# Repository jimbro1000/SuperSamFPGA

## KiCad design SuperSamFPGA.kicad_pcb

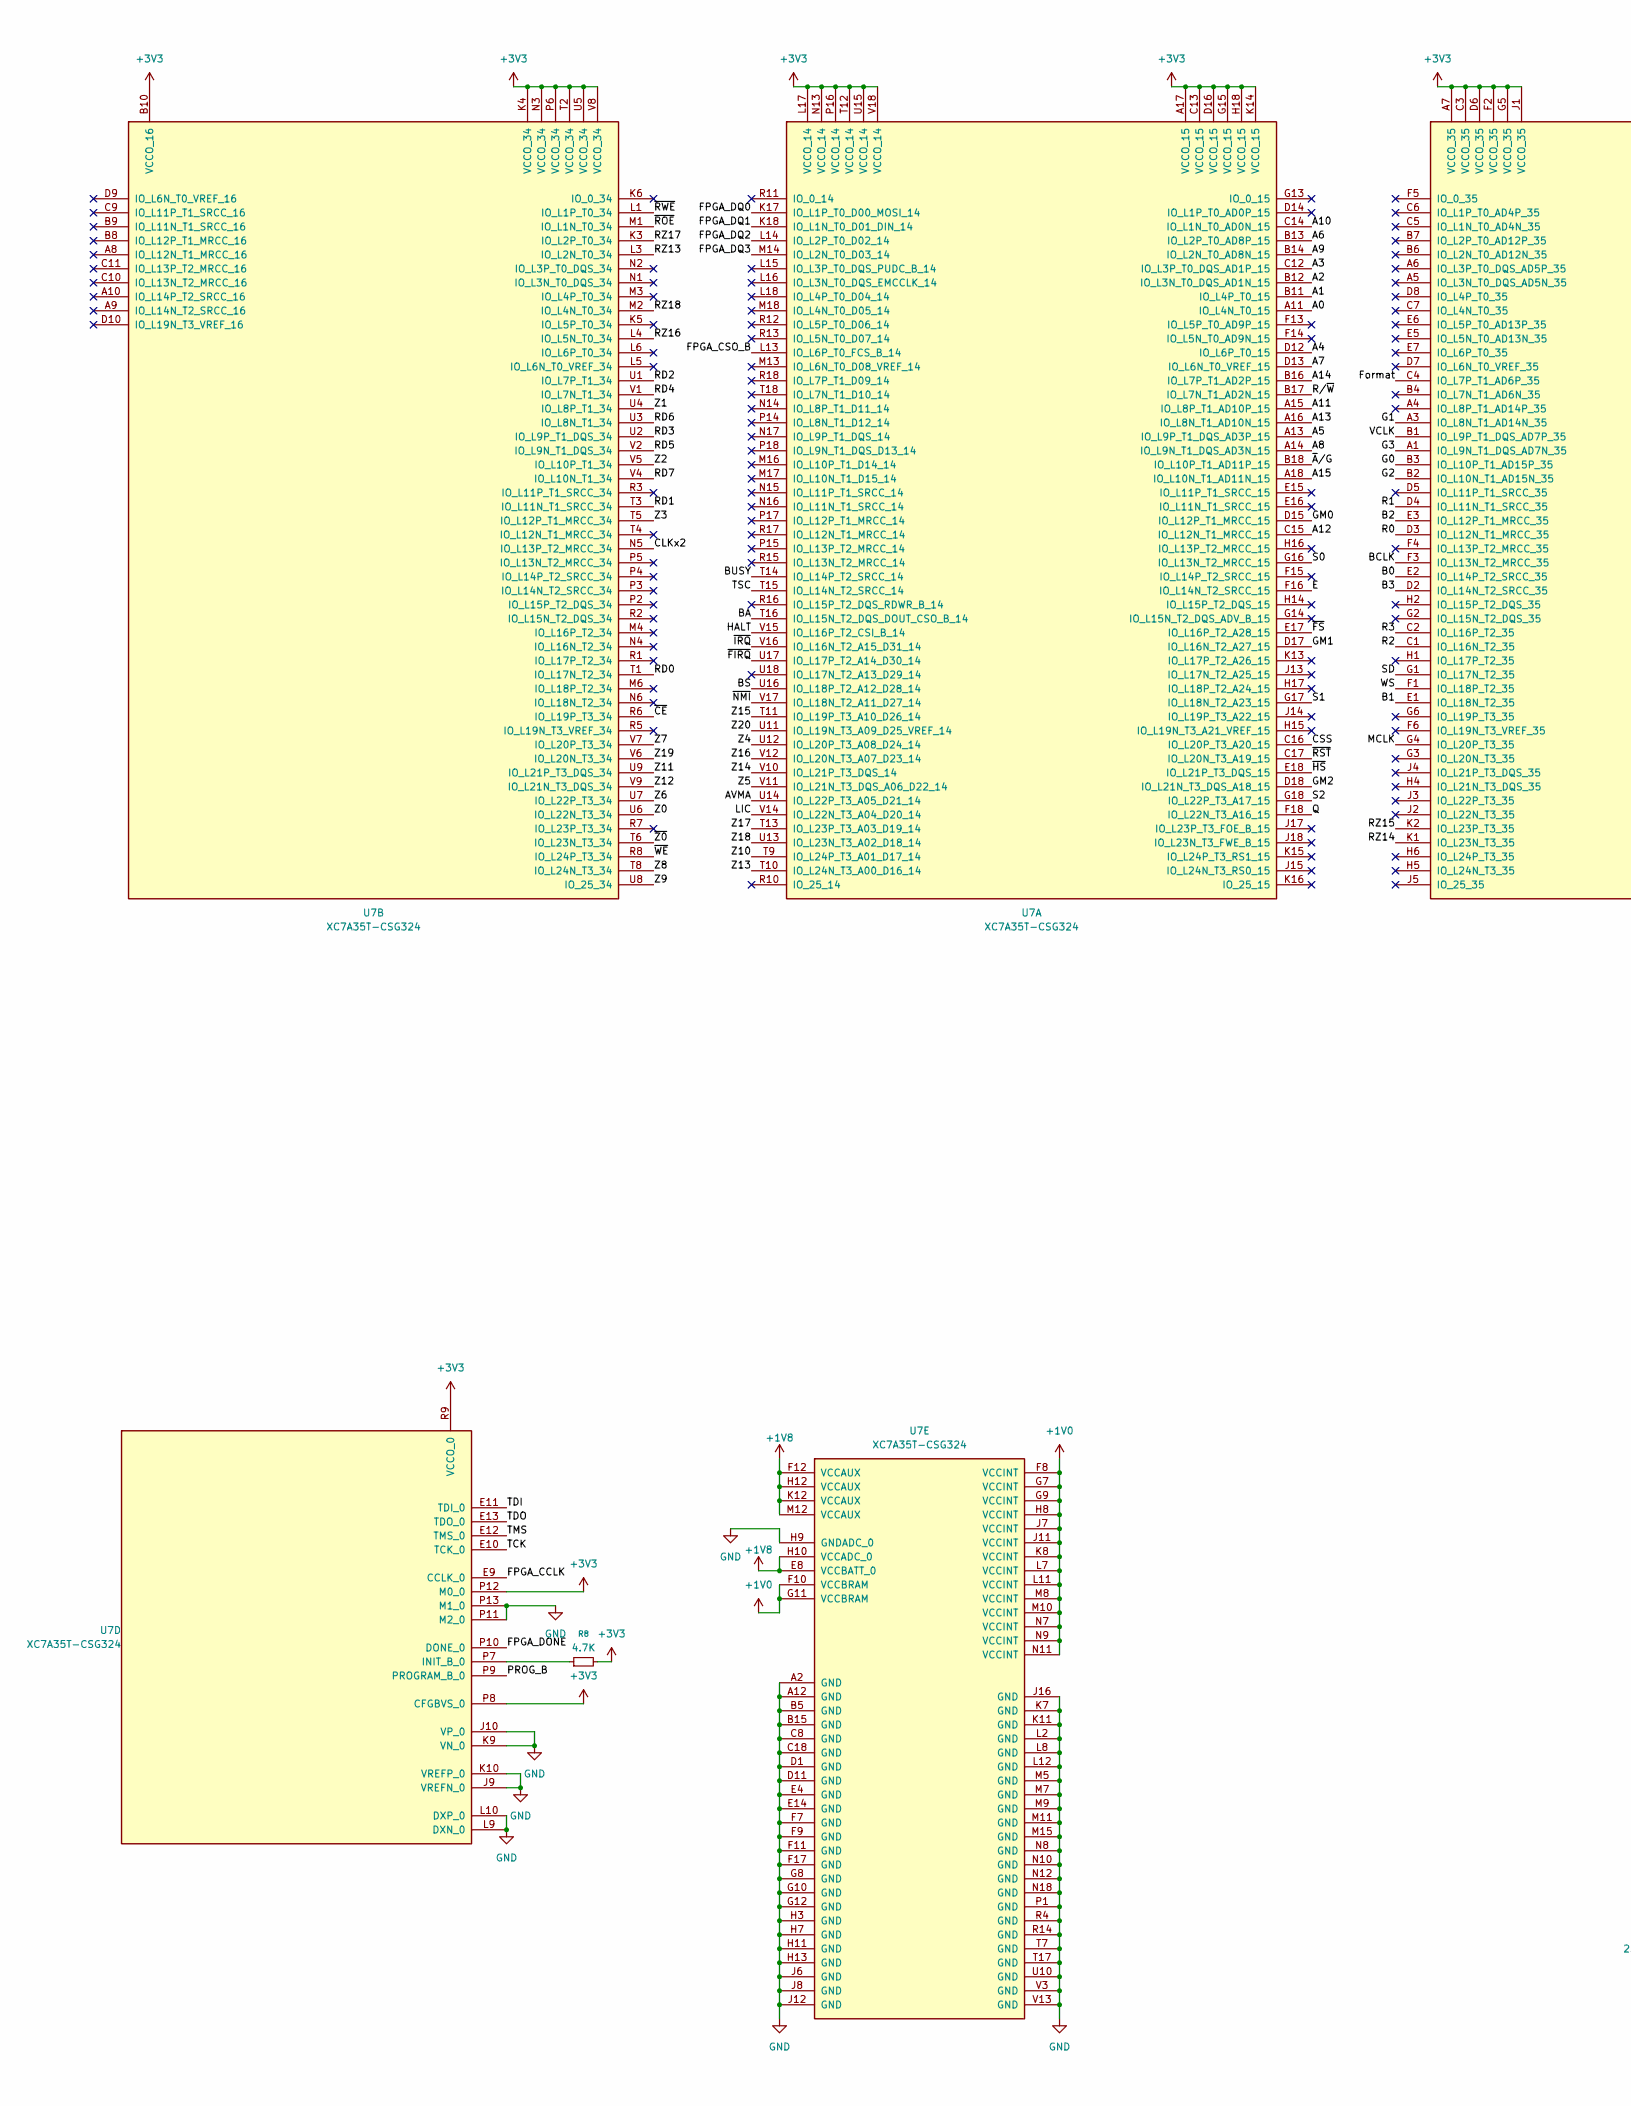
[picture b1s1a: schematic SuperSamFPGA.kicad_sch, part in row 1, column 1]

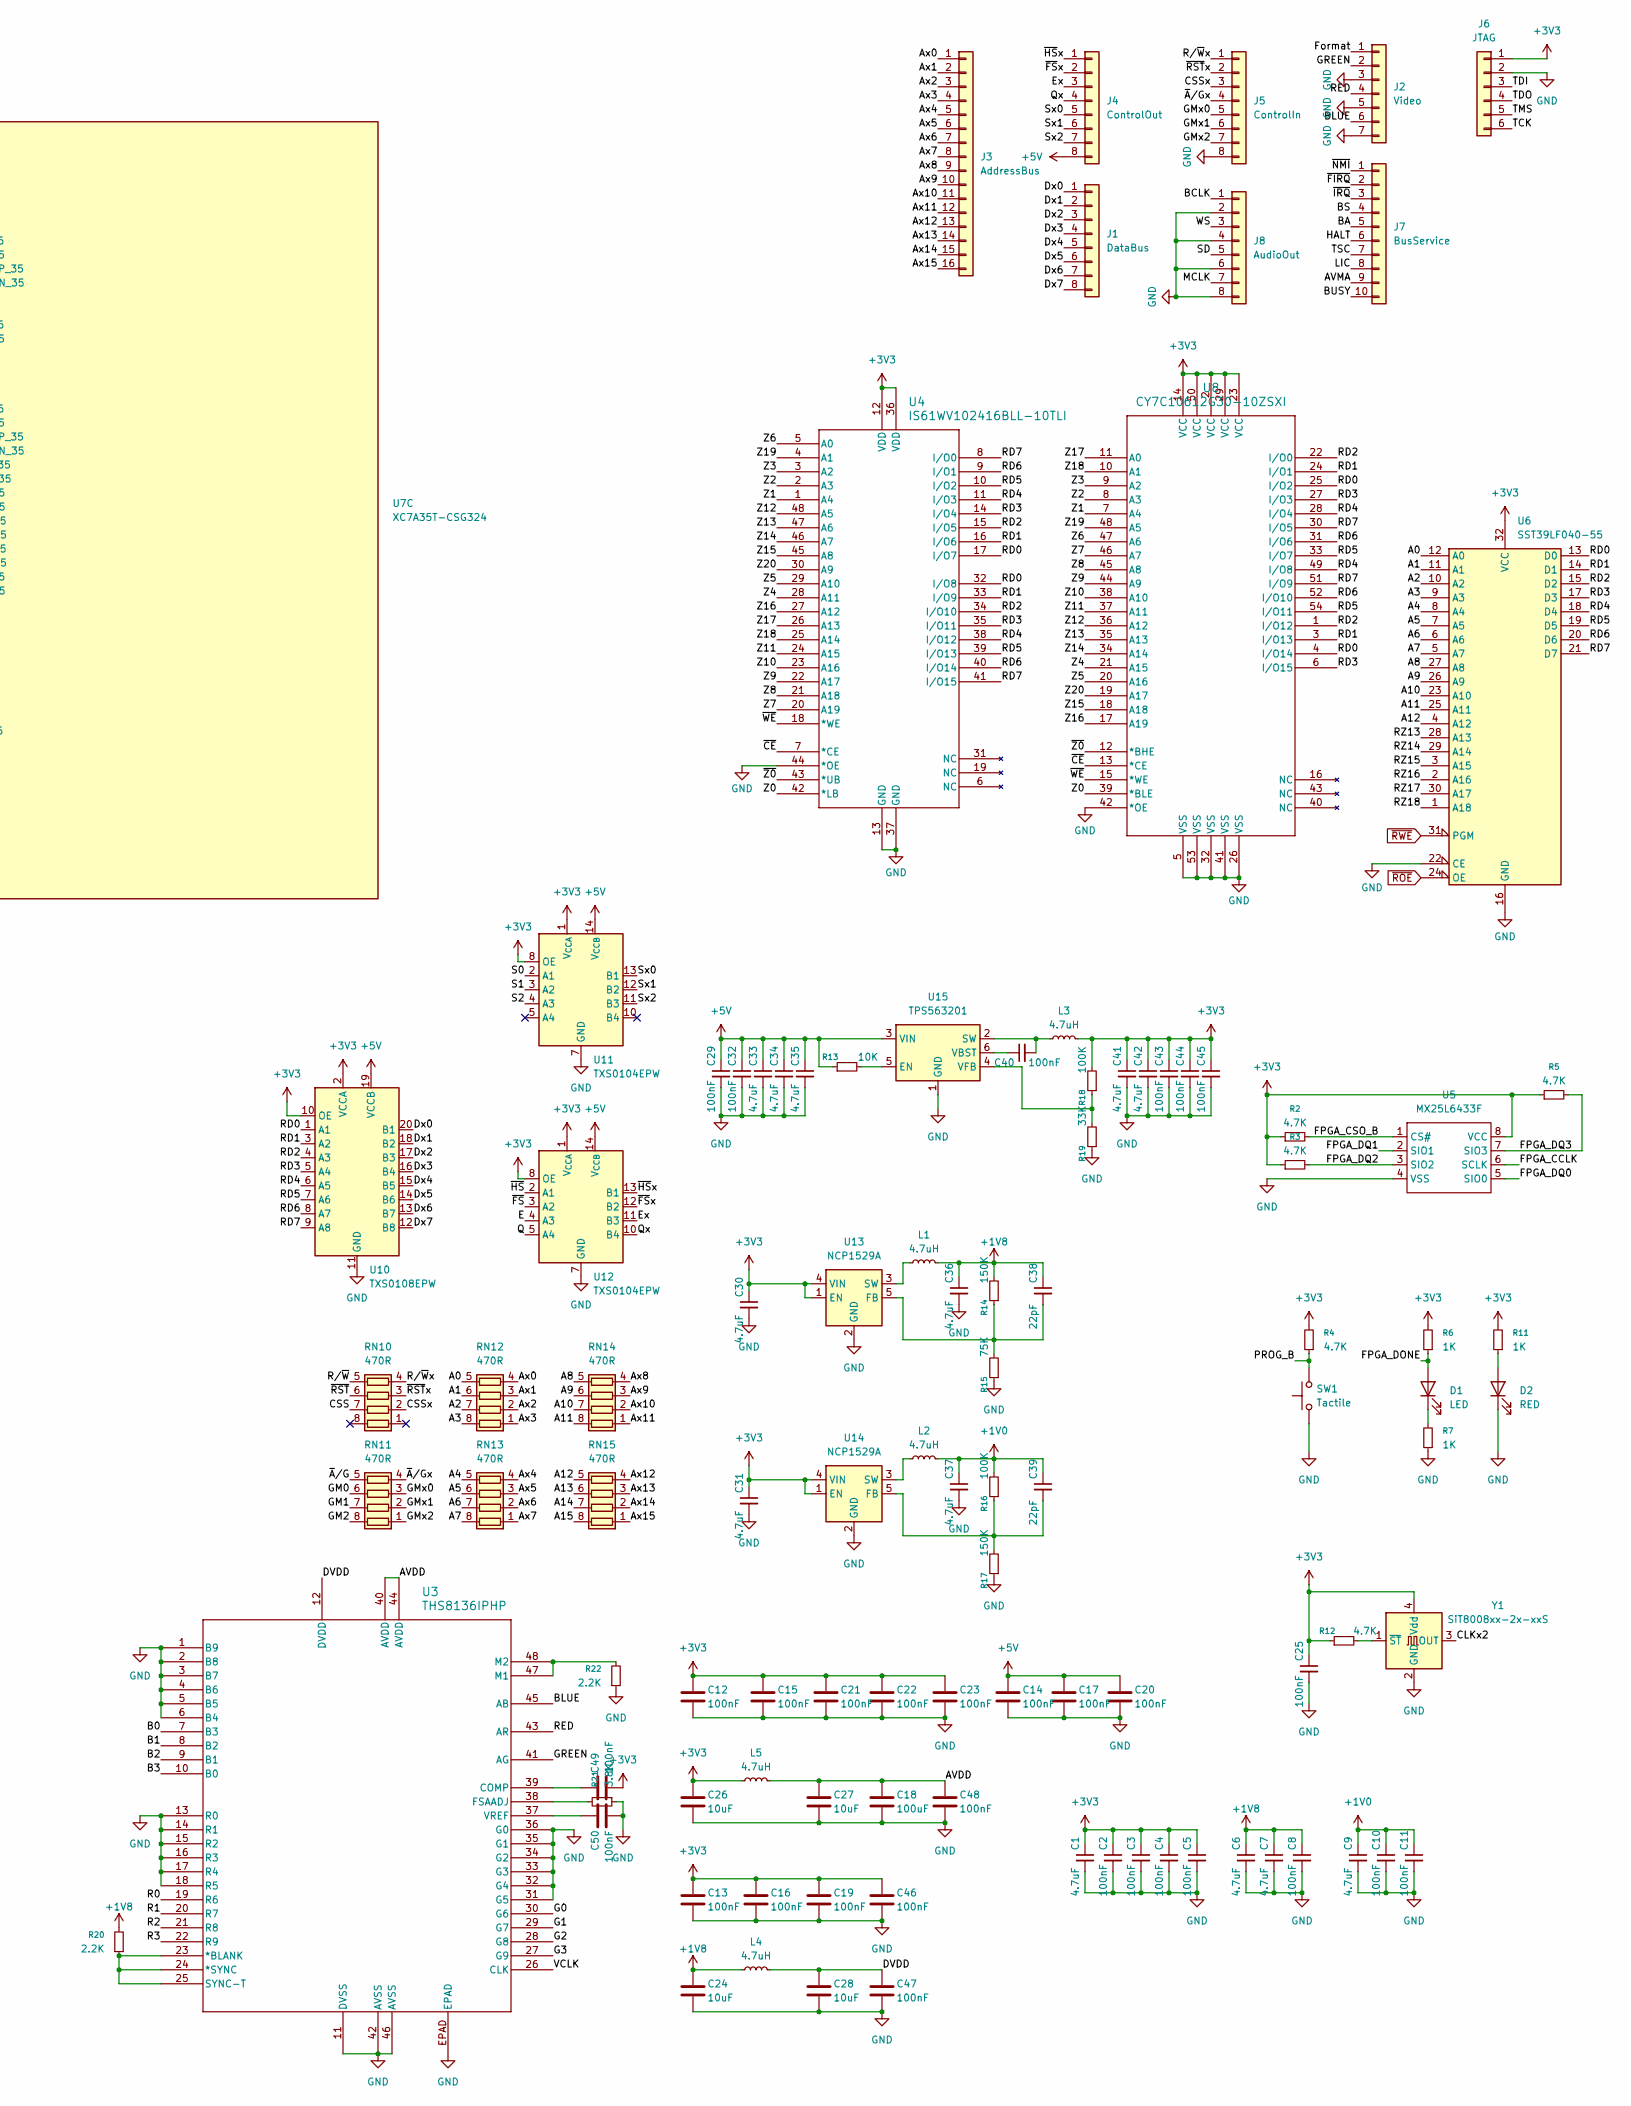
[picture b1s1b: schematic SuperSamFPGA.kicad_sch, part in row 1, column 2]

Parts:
C1, C6, C7, C9, C30, C31, C33, C34, C35, C36, C37, C41, C42: 4.7uF; C_0603_1608Metric; LCSC C1705
C2, C3, C4, C5, C8, C10, C11, C25, C29, C32, C40, C43, C44, C45: 100nF; C_0402_1005Metric; LCSC C1525
C12, C13, C14, C15, C16, C17, C19, C20, C21, C22, C23, C46, C47, C48, C49, C50: 100nF; C_0402_1005Metric; JLCPCB BOM 0
C18: 100uF; C_0805_2012Metric; JLCPCB BOM 0
C24, C26, C27, C28: 10uF; C_0805_2012Metric; JLCPCB BOM 0
C38, C39: 22pF; C_0402_1005Metric; LCSC C1555
D1: LED; LED_0603_1608Metric; LCSC C2290
D2: RED; LED_0603_1608Metric; LCSC C2286
J1: DataBus; PinHeader_1x08_P2.54mm_Vertical
J2: Video; PinHeader_1x07_P2.54mm_Vertical
J3: AddressBus; PinHeader_1x16_P2.54mm_Vertical
J4: ControlOut; PinHeader_1x08_P2.54mm_Vertical
J5: ControlIn; PinHeader_1x08_P2.54mm_Vertical
J6: JTAG; PinHeader_1x06_P2.54mm_Vertical
J7: BusService; PinHeader_1x10_P2.54mm_Vertical
J8: AudioOut; PinHeader_1x08_P2.54mm_Vertical
L1, L2, L4, L5: 4.7uH; L_0805_2012Metric; LCSC C86090
L3: 4.7uH; L_6.3x6.3_H3; LCSC C703091
R2, R3, R4, R5, R8: 4.7K; R_0402_1005Metric; LCSC C25900
R6, R7, R11: 1K; R_0402_1005Metric; LCSC C11702
R12: 4.7K; R_0603_1608Metric; LCSC C23162
R13: 10K; R_0402_1005Metric; LCSC C25744
R14, R17: 150K; R_0402_1005Metric; LCSC C93947
R15: 75K; R_0402_1005Metric; LCSC C25798
R16, R18: 100K; R_0402_1005Metric; LCSC C25741
R19: 33K; R_0402_1005Metric; LCSC C25779
R20, R22: 2.2K; R_0402_1005Metric; LCSC C25879
R21: 3.8K; R_0402_1005Metric; LCSC C852772
RN10, RN11, RN12, RN13, RN14, RN15: 470R; R_Array_Convex_4x0402; LCSC C425292
SW1: Tactile; SW_SPST_EVQPE1; LCSC C49108628
U3: THS8136IPHP; PHP48_4P1X4P1; DigiKey 296-23965-ND
U4: IS61WV102416BLL-10TLI; TSOP-I-48_18.4x12mm_P0.5mm; DigiKey 706-1055-ND
U5: MX25L6433F; SO-8_3.9x4.9mm_P1.27mm; LCSC C706695
U6: SST39LF040-55; PLCC-32_THT-Socket; DigiKey SST39LF040-55-4C-NHE-ND
U7: XC7A35T-CSG324; BGA-324_15x15mm_Layout18x18_P0.8mm
U8: CY7C10612G30-10ZSXI; TSOP-II-54_22.2x10.16mm_P0.8mm
U10: TXS0108EPW; TSSOP-20_4.4x6.5mm_P0.65mm; LCSC C17206
U11, U12: TXS0104EPW; TSSOP-14_4.4x5mm_P0.65mm; LCSC C44955
U13, U14: NCP1529A; SOT-23-5; LCSC C49375212
U15: TPS563201; SOT-23-6; LCSC C116592
Y1: SiT8008xx-2x-xxS; Oscillator_SMD_SiT_PQFN-4Pin_3.2x2.5mm; LCSC C2901579

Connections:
+1V0: C9.1, C10.1, C11.1, C37.1, C39.1, L2.2, R16.2, U7.F8 (VCCINT), U7.F10 (VCCBRAM), U7.G7 (VCCINT), U7.G9 (VCCINT), U7.G11 (VCCBRAM), U7.H8 (VCCINT), U7.J7 (VCCINT), U7.J11 (VCCINT), U7.K8 (VCCINT), U7.L7 (VCCINT), U7.L11 (VCCINT), U7.M8 (VCCINT), U7.M10 (VCCINT), U7.N7 (VCCINT), U7.N9 (VCCINT), U7.N11 (VCCINT)
+1V8: C6.1, C7.1, C8.1, C24.1, C36.1, C38.1, L1.2, L4.1, R14.2, R20.2, U7.E8 (VCCBATT_0), U7.F12 (VCCAUX), U7.H10 (VCCADC_0), U7.H12 (VCCAUX), U7.K12 (VCCAUX), U7.M12 (VCCAUX)
+3V3: C1.1, C2.1, C3.1, C4.1, C5.1, C12.1, C13.1, C15.1, C16.1, C19.1, C21.1, C22.1, C23.1, C25.1, C26.1, C30.1, C31.1, C41.1, C42.1, C43.1, C44.1, C45.1, C46.1, C49.2, J6.1, L3.2, L5.1, R2.1, R3.1, R4.2, R5.1, R6.2, R8.2, R11.2, R12.1, R18.2, U4.12 (VDD), U4.36 (VDD), U5.8 (VCC), U6.32 (VCC), U7.A7 (VCCO_35), U7.A17 (VCCO_15), U7.B10 (VCCO_16), U7.C3 (VCCO_35), U7.C13 (VCCO_15), U7.D6 (VCCO_35), U7.D16 (VCCO_15), U7.F2 (VCCO_35), U7.G5 (VCCO_35), U7.G15 (VCCO_15), U7.H18 (VCCO_15), U7.J1 (VCCO_35), U7.K4 (VCCO_34), U7.K14 (VCCO_15), U7.L17 (VCCO_14), U7.N3 (VCCO_34), U7.N13 (VCCO_14), U7.P6 (VCCO_34), U7.P8 (CFGBVS_0), U7.P12 (M0_0), U7.P16 (VCCO_14), U7.R9 (VCCO_0), U7.T2 (VCCO_34), U7.T12 (VCCO_14), U7.U5 (VCCO_34), U7.U15 (VCCO_14), U7.V8 (VCCO_34), U7.V18 (VCCO_14), U8.2 (VCC), U8.14 (VCC), U8.23 (VCC), U8.29 (VCC), U8.50 (VCC), U10.2 (VCCA), U10.10 (OE), U11.1 (V_{CCA}), U11.8 (OE), U12.1 (V_{CCA}), U12.8 (OE), U13.1 (EN), U13.4 (VIN), U14.1 (EN), U14.4 (VIN), Y1.4 (Vdd)
+5V: C14.1, C17.1, C20.1, C29.1, C32.1, C33.1, C34.1, C35.1, J4.8, R13.1, U10.19 (VCCB), U11.14 (V_{CCB}), U12.14 (V_{CCB}), U15.3 (VIN)
/A0: RN12.5 (R4.2), U6.12 (A0), U7.A11 (IO_L4N_T0_15)
/A1: RN12.6 (R3.2), U6.11 (A1), U7.B11 (IO_L4P_T0_15)
/A2: RN12.7 (R2.2), U6.10 (A2), U7.B12 (IO_L3N_T0_DQS_AD1N_15)
/A3: RN12.8 (R1.2), U6.9 (A3), U7.C12 (IO_L3P_T0_DQS_AD1P_15)
/A4: RN13.5 (R4.2), U6.8 (A4), U7.D12 (IO_L6P_T0_15)
/A5: RN13.6 (R3.2), U6.7 (A5), U7.A13 (IO_L9P_T1_DQS_AD3P_15)
/A6: RN13.7 (R2.2), U6.6 (A6), U7.B13 (IO_L2P_T0_AD8P_15)
/A7: RN13.8 (R1.2), U6.5 (A7), U7.D13 (IO_L6N_T0_VREF_15)
/A8: RN14.5 (R4.2), U6.27 (A8), U7.A14 (IO_L9N_T1_DQS_AD3N_15)
/A9: RN14.6 (R3.2), U6.26 (A9), U7.B14 (IO_L2N_T0_AD8N_15)
/A10: RN14.7 (R2.2), U6.23 (A10), U7.C14 (IO_L1N_T0_AD0N_15)
/A11: RN14.8 (R1.2), U6.25 (A11), U7.A15 (IO_L8P_T1_AD10P_15)
/A12: RN15.5 (R4.2), U6.4 (A12), U7.C15 (IO_L12N_T1_MRCC_15)
/A13: RN15.6 (R3.2), U7.A16 (IO_L8N_T1_AD10N_15)
/A14: RN15.7 (R2.2), U7.B16 (IO_L7P_T1_AD2P_15)
/A15: RN15.8 (R1.2), U7.A18 (IO_L10N_T1_AD11N_15)
/AVDD: C18.1, C27.1, C48.1, L5.2, U3.40 (AVDD), U3.44 (AVDD)
/AVMA: J7.9, U7.U14 (IO_L22P_T3_A05_D21_14)
/Ax0: J3.1, RN12.4 (R4.1)
/Ax1: J3.2, RN12.3 (R3.1)
/Ax2: J3.3, RN12.2 (R2.1)
/Ax3: J3.4, RN12.1 (R1.1)
/Ax4: J3.5, RN13.4 (R4.1)
/Ax5: J3.6, RN13.3 (R3.1)
/Ax6: J3.7, RN13.2 (R2.1)
/Ax7: J3.8, RN13.1 (R1.1)
/Ax8: J3.9, RN14.4 (R4.1)
/Ax9: J3.10, RN14.3 (R3.1)
/Ax10: J3.11, RN14.2 (R2.1)
/Ax11: J3.12, RN14.1 (R1.1)
/Ax12: J3.13, RN15.4 (R4.1)
/Ax13: J3.14, RN15.3 (R3.1)
/Ax14: J3.15, RN15.2 (R2.1)
/Ax15: J3.16, RN15.1 (R1.1)
/B0: U3.7 (B3), U7.E2 (IO_L14P_T2_SRCC_35)
/B1: U3.8 (B2), U7.E1 (IO_L18N_T2_35)
/B2: U3.9 (B1), U7.E3 (IO_L12P_T1_MRCC_35)
/B3: U3.10 (B0), U7.D2 (IO_L14N_T2_SRCC_35)
/BA: J7.5, U7.T16 (IO_L15N_T2_DQS_DOUT_CSO_B_14)
/BCLK: J8.1, U7.F3 (IO_L13N_T2_MRCC_35)
/BLUE: J2.6, U3.45 (AB)
/BS: J7.4, U7.U16 (IO_L18P_T2_A12_D28_14)
/BUSY: J7.10, U7.T14 (IO_L14P_T2_SRCC_14)
/CLKx2: U7.N5 (IO_L13P_T2_MRCC_34), Y1.3 (OUT)
/CSS: RN10.7 (R2.2), U7.C16 (IO_L20P_T3_A20_15)
/CSSx: J5.3, RN10.2 (R2.1)
/DVDD: C28.1, C47.1, L4.2, U3.12 (DVDD)
/Dx0: J1.1, U10.20 (B1)
/Dx1: J1.2, U10.18 (B2)
/Dx2: J1.3, U10.17 (B3)
/Dx3: J1.4, U10.16 (B4)
/Dx4: J1.5, U10.15 (B5)
/Dx5: J1.6, U10.14 (B6)
/Dx6: J1.7, U10.13 (B7)
/Dx7: J1.8, U10.12 (B8)
/E: U7.F16 (IO_L14N_T2_SRCC_15), U12.4 (A3)
/Ex: J4.3, U12.11 (B3)
/FPGA_CCLK: U5.6 (SCLK), U7.E9 (CCLK_0)
/FPGA_CSO_B: R2.2, U5.1 (CS#), U7.L13 (IO_L6P_T0_FCS_B_14)
/FPGA_DONE: D1.2 (A), R6.1, U7.P10 (DONE_0)
/FPGA_DQ0: U5.5 (SIO0), U7.K17 (IO_L1P_T0_D00_MOSI_14)
/FPGA_DQ1: U5.2 (SIO1), U7.K18 (IO_L1N_T0_D01_DIN_14)
/FPGA_DQ2: R3.2, U5.3 (SIO2), U7.L14 (IO_L2P_T0_D02_14)
/FPGA_DQ3: R5.2, U5.7 (SIO3), U7.M14 (IO_L2N_T0_D03_14)
/Format: J2.1, U7.C4 (IO_L7P_T1_AD6P_35)
/G0: U3.30 (G6), U7.B3 (IO_L10P_T1_AD15P_35)
/G1: U3.29 (G7), U7.A3 (IO_L8N_T1_AD14N_35)
/G2: U3.28 (G8), U7.B2 (IO_L10N_T1_AD15N_35)
/G3: U3.27 (G9), U7.A1 (IO_L9N_T1_DQS_AD7N_35)
/GM0: RN11.6 (R3.2), U7.D15 (IO_L12P_T1_MRCC_15)
/GM1: RN11.7 (R2.2), U7.D17 (IO_L16N_T2_A27_15)
/GM2: RN11.8 (R1.2), U7.D18 (IO_L21N_T3_DQS_A18_15)
/GMx0: J5.5, RN11.3 (R3.1)
/GMx1: J5.6, RN11.2 (R2.1)
/GMx2: J5.7, RN11.1 (R1.1)
/GREEN: J2.2, U3.41 (AG)
/HALT: J7.6, U7.V15 (IO_L16P_T2_CSI_B_14)
/LIC: J7.8, U7.V14 (IO_L22N_T3_A04_D20_14)
/MCLK: J8.7, U7.G4 (IO_L20P_T3_35)
/PROG_B: R4.1, SW1.2, U7.P9 (PROGRAM_B_0)
/Q: U7.F18 (IO_L22N_T3_A16_15), U12.5 (A4)
/Qx: J4.4, U12.10 (B4)
/R0: U3.19 (R6), U7.D3 (IO_L12N_T1_MRCC_35)
/R1: U3.20 (R7), U7.D4 (IO_L11N_T1_SRCC_35)
/R2: U3.21 (R8), U7.C1 (IO_L16N_T2_35)
/R3: U3.22 (R9), U7.C2 (IO_L16P_T2_35)
/RD0: U4.17 (I/O7), U4.32 (I/O8), U6.13 (D0), U7.T1 (IO_L17N_T2_34), U8.4 (I/O14), U8.25 (I/O2), U10.1 (A1)
/RD1: U4.16 (I/O6), U4.33 (I/O9), U6.14 (D1), U7.T3 (IO_L11N_T1_SRCC_34), U8.3 (I/O13), U8.24 (I/O1), U10.3 (A2)
/RD2: U4.15 (I/O5), U4.34 (I/O10), U6.15 (D2), U7.U1 (IO_L7P_T1_34), U8.1 (I/O12), U8.22 (I/O0), U10.4 (A3)
/RD3: U4.14 (I/O4), U4.35 (I/O11), U6.17 (D3), U7.U2 (IO_L9P_T1_DQS_34), U8.6 (I/O15), U8.27 (I/O3), U10.5 (A4)
/RD4: U4.11 (I/O3), U4.38 (I/O12), U6.18 (D4), U7.V1 (IO_L7N_T1_34), U8.28 (I/O4), U8.49 (I/O8), U10.6 (A5)
/RD5: U4.10 (I/O2), U4.39 (I/O13), U6.19 (D5), U7.V2 (IO_L9N_T1_DQS_34), U8.33 (I/O7), U8.54 (I/O11), U10.7 (A6)
/RD6: U4.9 (I/O1), U4.40 (I/O14), U6.20 (D6), U7.U3 (IO_L8N_T1_34), U8.31 (I/O6), U8.52 (I/O10), U10.8 (A7)
/RD7: U4.8 (I/O0), U4.41 (I/O15), U6.21 (D7), U7.V4 (IO_L10N_T1_34), U8.30 (I/O5), U8.51 (I/O9), U10.9 (A8)
/RED: J2.4, U3.43 (AR)
/RZ13: U6.28 (A13), U7.L3 (IO_L2N_T0_34)
/RZ14: U6.29 (A14), U7.K1 (IO_L23N_T3_35)
/RZ15: U6.3 (A15), U7.K2 (IO_L23P_T3_35)
/RZ16: U6.2 (A16), U7.L4 (IO_L5N_T0_34)
/RZ17: U6.30 (A17), U7.K3 (IO_L2P_T0_34)
/RZ18: U6.1 (A18), U7.M2 (IO_L4N_T0_34)
/R/~W: RN10.5 (R4.2), U7.B17 (IO_L7N_T1_AD2N_15)
/R/~Wx: J5.1, RN10.4 (R4.1)
/S0: U7.G16 (IO_L13N_T2_MRCC_15), U11.2 (A1)
/S1: U7.G17 (IO_L18N_T2_A23_15), U11.3 (A2)
/S2: U7.G18 (IO_L22P_T3_A17_15), U11.4 (A3)
/SD: J8.5, U7.G1 (IO_L17N_T2_35)
/Sx0: J4.5, U11.13 (B1)
/Sx1: J4.6, U11.12 (B2)
/Sx2: J4.7, U11.11 (B3)
/TCK: J6.6, U7.E10 (TCK_0)
/TDI: J6.3, U7.E11 (TDI_0)
/TDO: J6.4, U7.E13 (TDO_0)
/TMS: J6.5, U7.E12 (TMS_0)
/TSC: J7.7, U7.T15 (IO_L14N_T2_SRCC_14)
/VCLK: U3.26 (CLK), U7.B1 (IO_L9P_T1_DQS_AD7P_35)
/WS: J8.3, U7.F1 (IO_L18P_T2_35)
/Z0: U4.42 (*LB), U7.U6 (IO_L22N_T3_34), U8.39 (*BLE)
/Z1: U4.1 (A4), U7.U4 (IO_L8P_T1_34), U8.7 (A4)
/Z2: U4.2 (A3), U7.V5 (IO_L10P_T1_34), U8.8 (A3)
/Z3: U4.3 (A2), U7.T5 (IO_L12P_T1_MRCC_34), U8.9 (A2)
/Z4: U4.28 (A11), U7.U12 (IO_L20P_T3_A08_D24_14), U8.21 (A15)
/Z5: U4.29 (A10), U7.V11 (IO_L21N_T3_DQS_A06_D22_14), U8.20 (A16)
/Z6: U4.5 (A0), U7.U7 (IO_L22P_T3_34), U8.47 (A6)
/Z7: U4.20 (A19), U7.V7 (IO_L20P_T3_34), U8.46 (A7)
/Z8: U4.21 (A18), U7.T8 (IO_L24N_T3_34), U8.45 (A8)
/Z9: U4.22 (A17), U7.U8 (IO_25_34), U8.44 (A9)
/Z10: U4.23 (A16), U7.T9 (IO_L24P_T3_A01_D17_14), U8.38 (A10)
/Z11: U4.24 (A15), U7.U9 (IO_L21P_T3_DQS_34), U8.37 (A11)
/Z12: U4.48 (A5), U7.V9 (IO_L21N_T3_DQS_34), U8.36 (A12)
/Z13: U4.47 (A6), U7.T10 (IO_L24N_T3_A00_D16_14), U8.35 (A13)
/Z14: U4.46 (A7), U7.V10 (IO_L21P_T3_DQS_14), U8.34 (A14)
/Z15: U4.45 (A8), U7.T11 (IO_L19P_T3_A10_D26_14), U8.18 (A18)
/Z16: U4.27 (A12), U7.V12 (IO_L20N_T3_A07_D23_14), U8.17 (A19)
/Z17: U4.26 (A13), U7.T13 (IO_L23P_T3_A03_D19_14), U8.11 (A0)
/Z18: U4.25 (A14), U7.U13 (IO_L23N_T3_A02_D18_14), U8.10 (A1)
/Z19: U4.4 (A1), U7.V6 (IO_L20N_T3_34), U8.48 (A5)
/Z20: U4.30 (A9), U7.U11 (IO_L19N_T3_A09_D25_VREF_14), U8.19 (A17)
/~A/G: RN11.5 (R4.2), U7.B18 (IO_L10P_T1_AD11P_15)
/~A/Gx: J5.4, RN11.4 (R4.1)
/~CE: U4.7 (*CE), U7.R6 (IO_L19P_T3_34), U8.13 (*CE)
/~FIRQ: J7.2, U7.U17 (IO_L17P_T2_A14_D30_14)
/~FS: U7.E17 (IO_L16P_T2_A28_15), U12.3 (A2)
/~FSx: J4.2, U12.12 (B2)
/~HS: U7.E18 (IO_L21P_T3_DQS_15), U12.2 (A1)
/~HSx: J4.1, U12.13 (B1)
/~IRQ: J7.3, U7.V16 (IO_L16N_T2_A15_D31_14)
/~NMI: J7.1, U7.V17 (IO_L18N_T2_A11_D27_14)
/~RST: RN10.6 (R3.2), U7.C17 (IO_L20N_T3_A19_15)
/~RSTx: J5.2, RN10.3 (R3.1)
/~WE: U4.18 (*WE), U7.R8 (IO_L24P_T3_34), U8.15 (*WE)
/~Z0: U4.43 (*UB), U7.T6 (IO_L23N_T3_34), U8.12 (*BHE)
GND: C1.2, C2.2, C3.2, C4.2, C5.2, C6.2, C7.2, C8.2, C9.2, C10.2, C11.2, C12.2, C13.2, C14.2, C15.2, C16.2, C17.2, C18.2, C19.2, C20.2, C21.2, C22.2, C23.2, C24.2, C25.2, C26.2, C27.2, C28.2, C29.2, C30.2, C31.2, C32.2, C33.2, C34.2, C35.2, C36.2, C37.2, C41.2, C42.2, C43.2, C44.2, C45.2, C46.2, C47.2, C48.2, C50.2, D2.1 (K), J2.3, J2.5, J2.7, J5.8, J6.2, J8.2, J8.4, J8.6, J8.8, R7.1, R15.1, R17.1, R19.1, R21.1, R22.1, SW1.1, U3.1 (B9), U3.2 (B8), U3.3 (B7), U3.4 (B6), U3.5 (B5), U3.6 (B4), U3.11 (DVSS), U3.13 (R0), U3.14 (R1), U3.15 (R2), U3.16 (R3), U3.17 (R4), U3.18 (R5), U3.31 (G5), U3.32 (G4), U3.33 (G3), U3.34 (G2), U3.35 (G1), U3.36 (G0), U3.42 (AVSS), U3.46 (AVSS), U3.EPAD, U4.13 (GND), U4.37 (GND), U4.44 (*OE), U5.4 (VSS), U6.16 (GND), U6.22 (CE), U7.A2 (GND), U7.A12 (GND), U7.B5 (GND), U7.B15 (GND), U7.C8 (GND), U7.C18 (GND), U7.D1 (GND), U7.D11 (GND), U7.E4 (GND), U7.E14 (GND), U7.F7 (GND), U7.F9 (GND), U7.F11 (GND), U7.F17 (GND), U7.G8 (GND), U7.G10 (GND), U7.G12 (GND), U7.H3 (GND), U7.H7 (GND), U7.H9 (GNDADC_0), U7.H11 (GND), U7.H13 (GND), U7.J6 (GND), U7.J8 (GND), U7.J9 (VREFN_0), U7.J10 (VP_0), U7.J12 (GND), U7.J16 (GND), U7.K7 (GND), U7.K9 (VN_0), U7.K10 (VREFP_0), U7.K11 (GND), U7.L2 (GND), U7.L8 (GND), U7.L9 (DXN_0), U7.L10 (DXP_0), U7.L12 (GND), U7.M5 (GND), U7.M7 (GND), U7.M9 (GND), U7.M11 (GND), U7.M15 (GND), U7.N8 (GND), U7.N10 (GND), U7.N12 (GND), U7.N18 (GND), U7.P1 (GND), U7.P11 (M2_0), U7.P13 (M1_0), U7.R4 (GND), U7.R14 (GND), U7.T7 (GND), U7.T17 (GND), U7.U10 (GND), U7.V3 (GND), U7.V13 (GND), U8.5 (VSS), U8.26 (VSS), U8.32 (VSS), U8.41 (VSS), U8.42 (*OE), U8.53 (VSS), U10.11 (GND), U11.7 (GND), U12.7 (GND), U13.2 (GND), U14.2 (GND), U15.1 (GND), Y1.2 (GND)
unnamed: D1.1 (K), R7.2
unnamed: D2.2 (A), R11.1
unnamed: R20.1, U3.23 (*BLANK), U3.24 (*SYNC), U3.25 (SYNC-T)
unnamed: C49.1, U3.39 (COMP)
unnamed: R21.2, U3.38 (FSAADJ)
unnamed: R22.2, U3.47 (M1), U3.48 (M2)
unnamed: C50.1, U3.37 (VREF)
unnamed: R8.1, U7.P7 (INIT_B_0)
unnamed: C38.2, R14.1, R15.2, U13.5 (FB)
unnamed: L1.1, U13.3 (SW)
unnamed: C39.2, R16.1, R17.2, U14.5 (FB)
unnamed: L2.1, U14.3 (SW)
unnamed: R13.2, U15.5 (EN)
unnamed: C40.2, L3.1, U15.2 (SW)
unnamed: C40.1, U15.6 (VBST)
unnamed: R18.1, R19.2, U15.4 (VFB)
unnamed: R12.2, Y1.1 (~ST)
~ROE: U6.24 (OE), U7.M1 (IO_L1N_T0_34)
~RWE: U6.31 (PGM), U7.L1 (IO_L1P_T0_34)

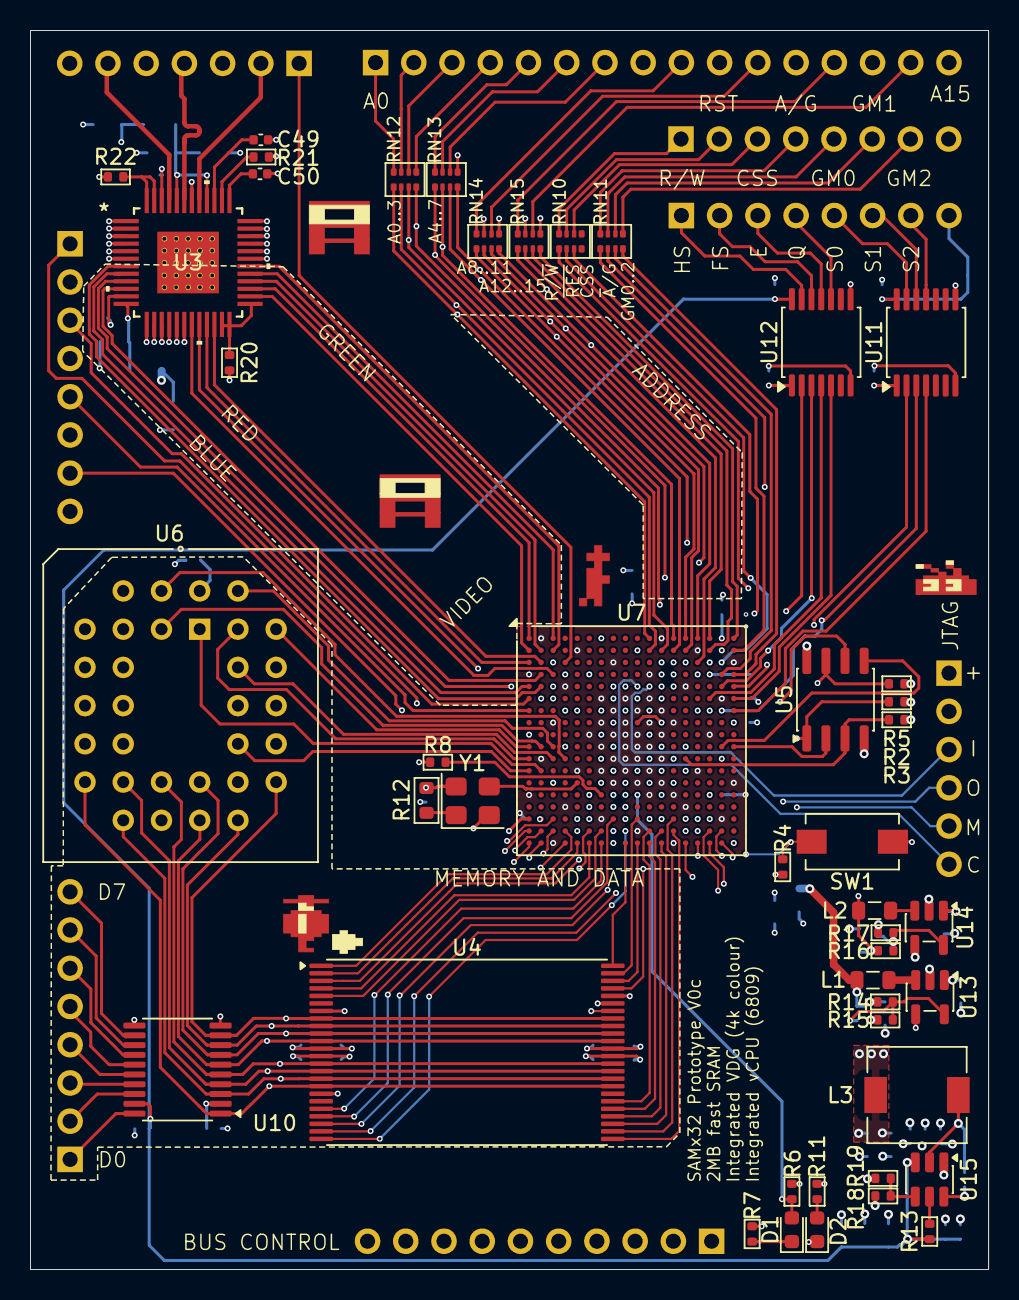
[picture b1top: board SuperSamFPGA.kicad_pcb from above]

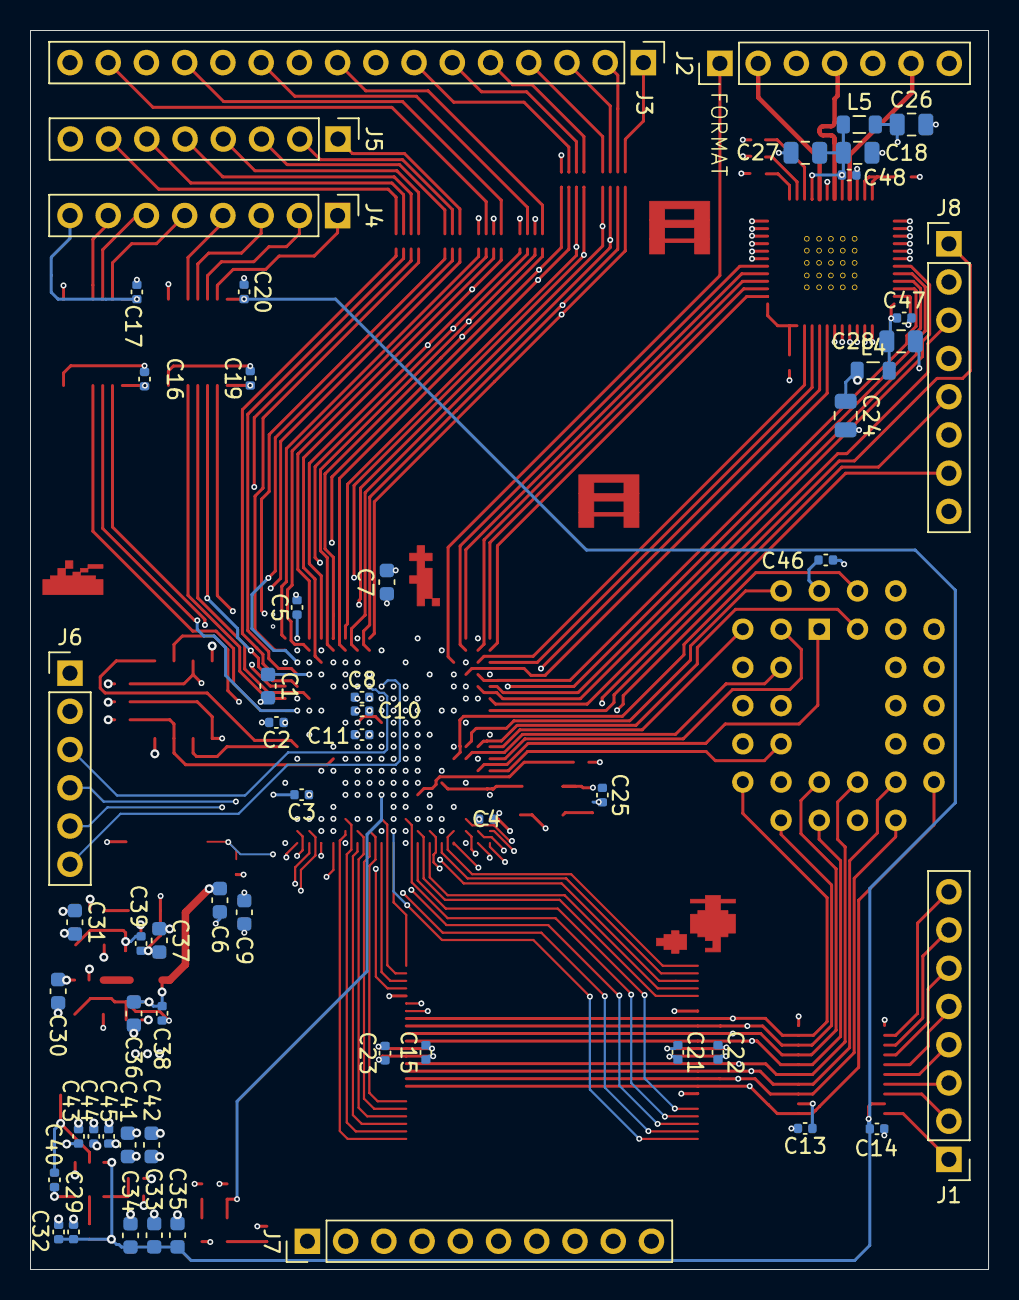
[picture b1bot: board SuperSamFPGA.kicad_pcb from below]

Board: 6 copper layers, 63.7 x 82.3 mm, 102 parts (57 on the bottom side), 176 nets.

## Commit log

2026-04-25 complete initial design
2026-04-25 implement alternative sram
2026-04-25 switch to single chip dac
2026-04-25 production ready
2026-06-06 refine design
2026-06-06 complete primary routing
